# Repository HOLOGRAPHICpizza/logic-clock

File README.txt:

Digital "synchronous" clock in 4000 series logic w/ incremental volume alarm and optional time set via RS-232.

By Michael Craft.

Released under the 2-Clause BSD License.

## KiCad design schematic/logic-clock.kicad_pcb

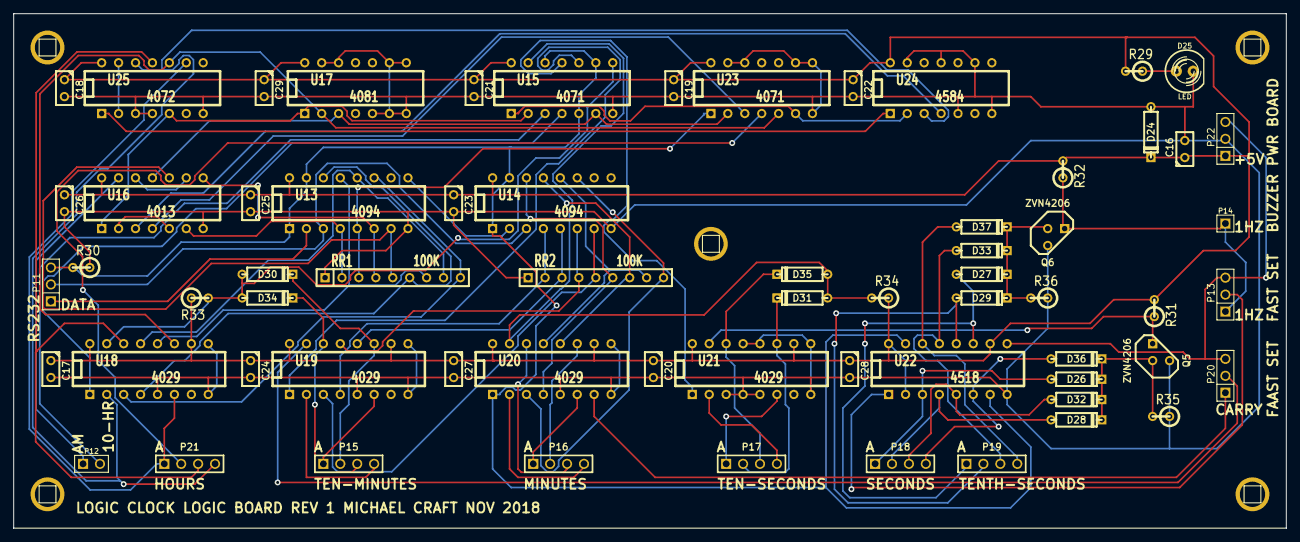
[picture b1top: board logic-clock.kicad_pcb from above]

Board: 2 copper layers, 191.0 x 77.2 mm, 65 parts (0 on the bottom side), 72 nets.

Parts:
C16: 1uF; C1
C17, C18, C19, C20, C21, C22, C23, C24, C25, C26, C27, C28, C29: 100nF; C1
D24, D26, D27, D28, D29, D30, D31, D32, D33, D34, D35, D36, D37: DIODE; D3
D25: LED; LED-5MM
P11, P13, P20, P22: 3-PIN_HEADER; PIN_ARRAY_3X1
P12: 2-PIN_HEADER; PIN_ARRAY_2X1
P14: 1-PIN_HEADER; PIN_ARRAY_1
P15, P16, P17, P18, P19, P21: 4-PIN_HEADER; PIN_ARRAY_4x1
Q5, Q6: ZVN4206; TO92DGS
R29: 1K; R1
R30, R31, R32, R33, R34, R35, R36: 100K; R1
RR1, RR2: 100K; SIL-9
U13, U14: 4094; DIP-16__300
U15, U23: 4071; DIP-14__300
U16: 4013; DIP-14__300
U17: 4081; DIP-14__300
U18, U19, U20, U21: 4029; DIP-16__300
U22: 4518; DIP-16__300
U24: 4584; DIP-14__300
U25: 4072; DIP-14__300

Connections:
1Hz: P13.1, P14.1, Q6.D, R32.1
+5V: C16.1, C17.1, C18.1, C19.1, C20.1, C21.1, C22.1, C23.1, C24.1, C25.1, C26.1, C27.1, C28.1, C29.1, D24.2, P22.1, R29.2, R31.2, R32.2, R33.1, R34.1, U13.16, U14.16, U15.14, U16.14, U17.14, U18.10, U18.16, U19.10, U19.16, U20.10, U20.16, U21.10, U21.16, U22.2, U22.10, U22.16, U23.14, U24.14, U25.14
/comparator-board/3A: P16.1, U20.6
/comparator-board/3B: P16.2, U20.11
/comparator-board/3C: P16.3, U20.14
/comparator-board/3D: P16.4, U20.2
/comparator-board/4A: P15.1, U19.6
/comparator-board/4B: D30.2, P15.2, U19.11
/comparator-board/4C: D34.2, P15.3, U19.14
/comparator-board/4D: P15.4, U19.2
/comparator-board/5A: P21.1, U18.6, U25.9
/comparator-board/5B: P21.2, U23.4
/comparator-board/5C: P21.3, U18.14, U25.11
/comparator-board/5D: P21.4, U18.2, U24.3, U25.12
/comparator-board/AM: P12.1, U16.13
/comparator-board/TEN-HOURS: P12.2, U15.3
/display-board/0A: D27.1, P19.1, U22.11
/display-board/0B: D29.1, P19.2, U22.12
/display-board/0C: D33.1, P19.3, U22.13
/display-board/0D: D37.1, P19.4, U22.14
/display-board/1A: D26.1, P18.1, U22.3
/display-board/1B: D28.1, P18.2, U22.4
/display-board/1C: D32.1, P18.3, U22.5
/display-board/1D: D36.1, P18.4, U22.6
/display-board/2A: P17.1, U21.6
/display-board/2B: D31.2, P17.2, U21.11
/display-board/2C: D35.2, P17.3, U21.14
/display-board/2D: P17.4, U21.2
/logic-board/10Hz: P13.3, P20.3, P22.3, U22.9
/logic-board/CLOCK: P11.2, U13.3, U14.3
/logic-board/DATA: P11.1, U13.2
/logic-board/MIN-CARRY: P20.1, U20.7
/logic-board/SEC_CLOCK: P13.2, U22.1
/logic-board/TEN-MIN_CLOCK: P20.2, U19.15
GND: C16.2, C17.2, C18.2, C19.2, C20.2, C21.2, C22.2, C23.2, C24.2, C25.2, C26.2, C27.2, C28.2, C29.2, D24.1, D25.2, P22.2, Q5.S, Q6.S, R30.1, R35.1, R36.1, RR1.1, RR2.1, U13.8, U14.8, U15.7, U16.7, U17.5, U17.6, U17.7, U17.8, U17.9, U17.12, U17.13, U18.5, U18.8, U18.9, U19.5, U19.8, U19.9, U20.5, U20.8, U20.9, U21.3, U21.4, U21.5, U21.8, U21.9, U21.12, U21.13, U22.8, U23.7, U23.8, U23.9, U23.12, U23.13, U24.5, U24.7, U24.9, U24.11, U24.13, U25.3, U25.4, U25.7
unnamed: RR1.6, U13.14, U18.4
unnamed: RR1.5, U13.7, U16.10
unnamed: RR1.4, U13.6, U16.8
unnamed: RR2.9, U14.11, U20.3
unnamed: RR2.8, U14.12, U20.13
unnamed: RR2.7, U14.13, U20.12
unnamed: RR2.6, U14.14, U20.4
unnamed: RR2.5, U14.7, U19.3
unnamed: RR2.4, U14.6, U19.13
unnamed: RR2.3, U14.5, U19.12
unnamed: RR1.7, U13.13, U18.12
unnamed: RR1.8, U13.12, U18.13
unnamed: RR1.9, U13.11, U18.3
unnamed: U15.11, U21.1
unnamed: U15.10, U19.1
unnamed: RR1.2, U13.4, U16.6
unnamed: RR2.2, U14.4, U19.4
unnamed: U24.1, U25.1
unnamed: U25.2, U25.13
unnamed: U15.1, U23.6, U24.2
unnamed: U15.4, U18.1
unnamed: U16.9, U16.12
unnamed: U13.9, U14.2
unnamed: U16.2, U16.5
unnamed: RR1.3, U13.5, U23.1
unnamed: U15.6, U16.11, U17.3, U23.2
unnamed: U17.2, U18.11, U23.5, U25.10
unnamed: U16.3, U24.4
unnamed: U15.2, U16.1, U17.1, U25.5
unnamed: U16.4, U23.3
unnamed: D31.1, D35.1, R34.2, U15.13, U20.15
unnamed: D27.2, D29.2, D33.2, D37.2, Q6.G, R36.2
unnamed: D26.2, D28.2, D32.2, D36.2, Q5.G, R35.2
unnamed: Q5.D, R31.1, U21.15
unnamed: D25.1, R29.1
SET: P11.3, R30.2, U13.1, U13.15, U14.1, U14.15, U15.5, U15.9, U15.12, U20.1, U22.7, U22.15
TEN-MIN_CARRY: D30.1, D34.1, R33.2, U15.8, U18.15

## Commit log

2016-04-18 added custom parts library
2016-04-18 woops
2016-04-18 added stuff
2016-04-18 changed pull-down resistor
2016-04-18 deleted some stuff...
2016-04-18 enhanced input protection
2016-04-18 better volume ramp
2016-05-30 cleanup kicad project
2016-05-30 cleaned up kicad project more
2016-05-30 started pcb
2016-05-30 display board schematic
2016-05-31 pcb rev 1
2016-05-31 pcb rev 2
2016-05-31 pcb rev 3
2016-06-25 lots of stuff
2016-06-25 PWM improved
2016-06-28 PWM improved again lol
2016-06-29 transmits zeros to clear shift registers
2016-06-29 transmits two zeros
2016-07-15 working on schematic...
2016-07-15 one more digit
2016-08-15 schematic matches prototype
2016-08-15 ok now it is correct mostly
2016-08-15 added shift registers
2016-08-15 ok i think this should be hooked up right
2016-08-15 resized page
2016-08-23 1st digit bug fix, disabled TX zeros
2016-08-23 2nd digit bug fix
2016-08-23 reset bug fix
2016-08-25 added display pwm board
2016-08-28 schematic is "done"
2016-08-28 added fast set
2016-08-28 added note
2016-08-28 upgraded set-logic-clock
2016-08-29 started rs232 board
2016-11-08 I HAVE NO IDEA
2016-11-20 minutes and seconds digits confirmed working, hours needs work
2016-11-20 added some resistors, works better
2018-10-29 replaced some diode gates with CMOS gates
2018-11-08 idk what changed i hope nothing is broken
2018-11-19 prototype works!
2018-11-19 passes ERC
2018-11-20 ready to lay out pcb
2018-11-23 layout almost ready for routing
2018-11-23 minor schematic edit and new netlist
2018-11-23 fixed unused chip connections
2018-11-24 half laid out, fixed netlist again
2018-11-24 about to try some sort of autorouter
2018-11-24 ready for autorouter
2018-11-24 actually ready for autoroute
2018-11-24 autoroute complete
2018-11-24 "done"
2018-11-24 added drill holes, should be ready for manufacture
2018-11-24 submitted for manufacture
2018-11-27 working on RS232 receiver
2018-11-27 still working on rs232
2018-11-27 cleaning up
2018-11-28 RS232 should be done now, still untested
2018-11-28 added rs232 output buffer
2018-11-28 simplified RS232, bench test successful, needs tested against actual logic board
2018-12-09 set-logic-clock updated to use rs232 circuit and take arguments
2018-12-10 changed argument format
2018-12-15 time setting script
2019-01-12 RS232 board REV 3
2019-01-13 started comparator board
2019-01-27 "v1.0" Schematics are "finished". Final assembly is not yet complete and changes may be required. Everything has been tested, at least by itself.
2019-01-28 deleted old pdf
2019-02-22 added layout document
2019-09-08 automatic setting works now, plus other unknown changes
